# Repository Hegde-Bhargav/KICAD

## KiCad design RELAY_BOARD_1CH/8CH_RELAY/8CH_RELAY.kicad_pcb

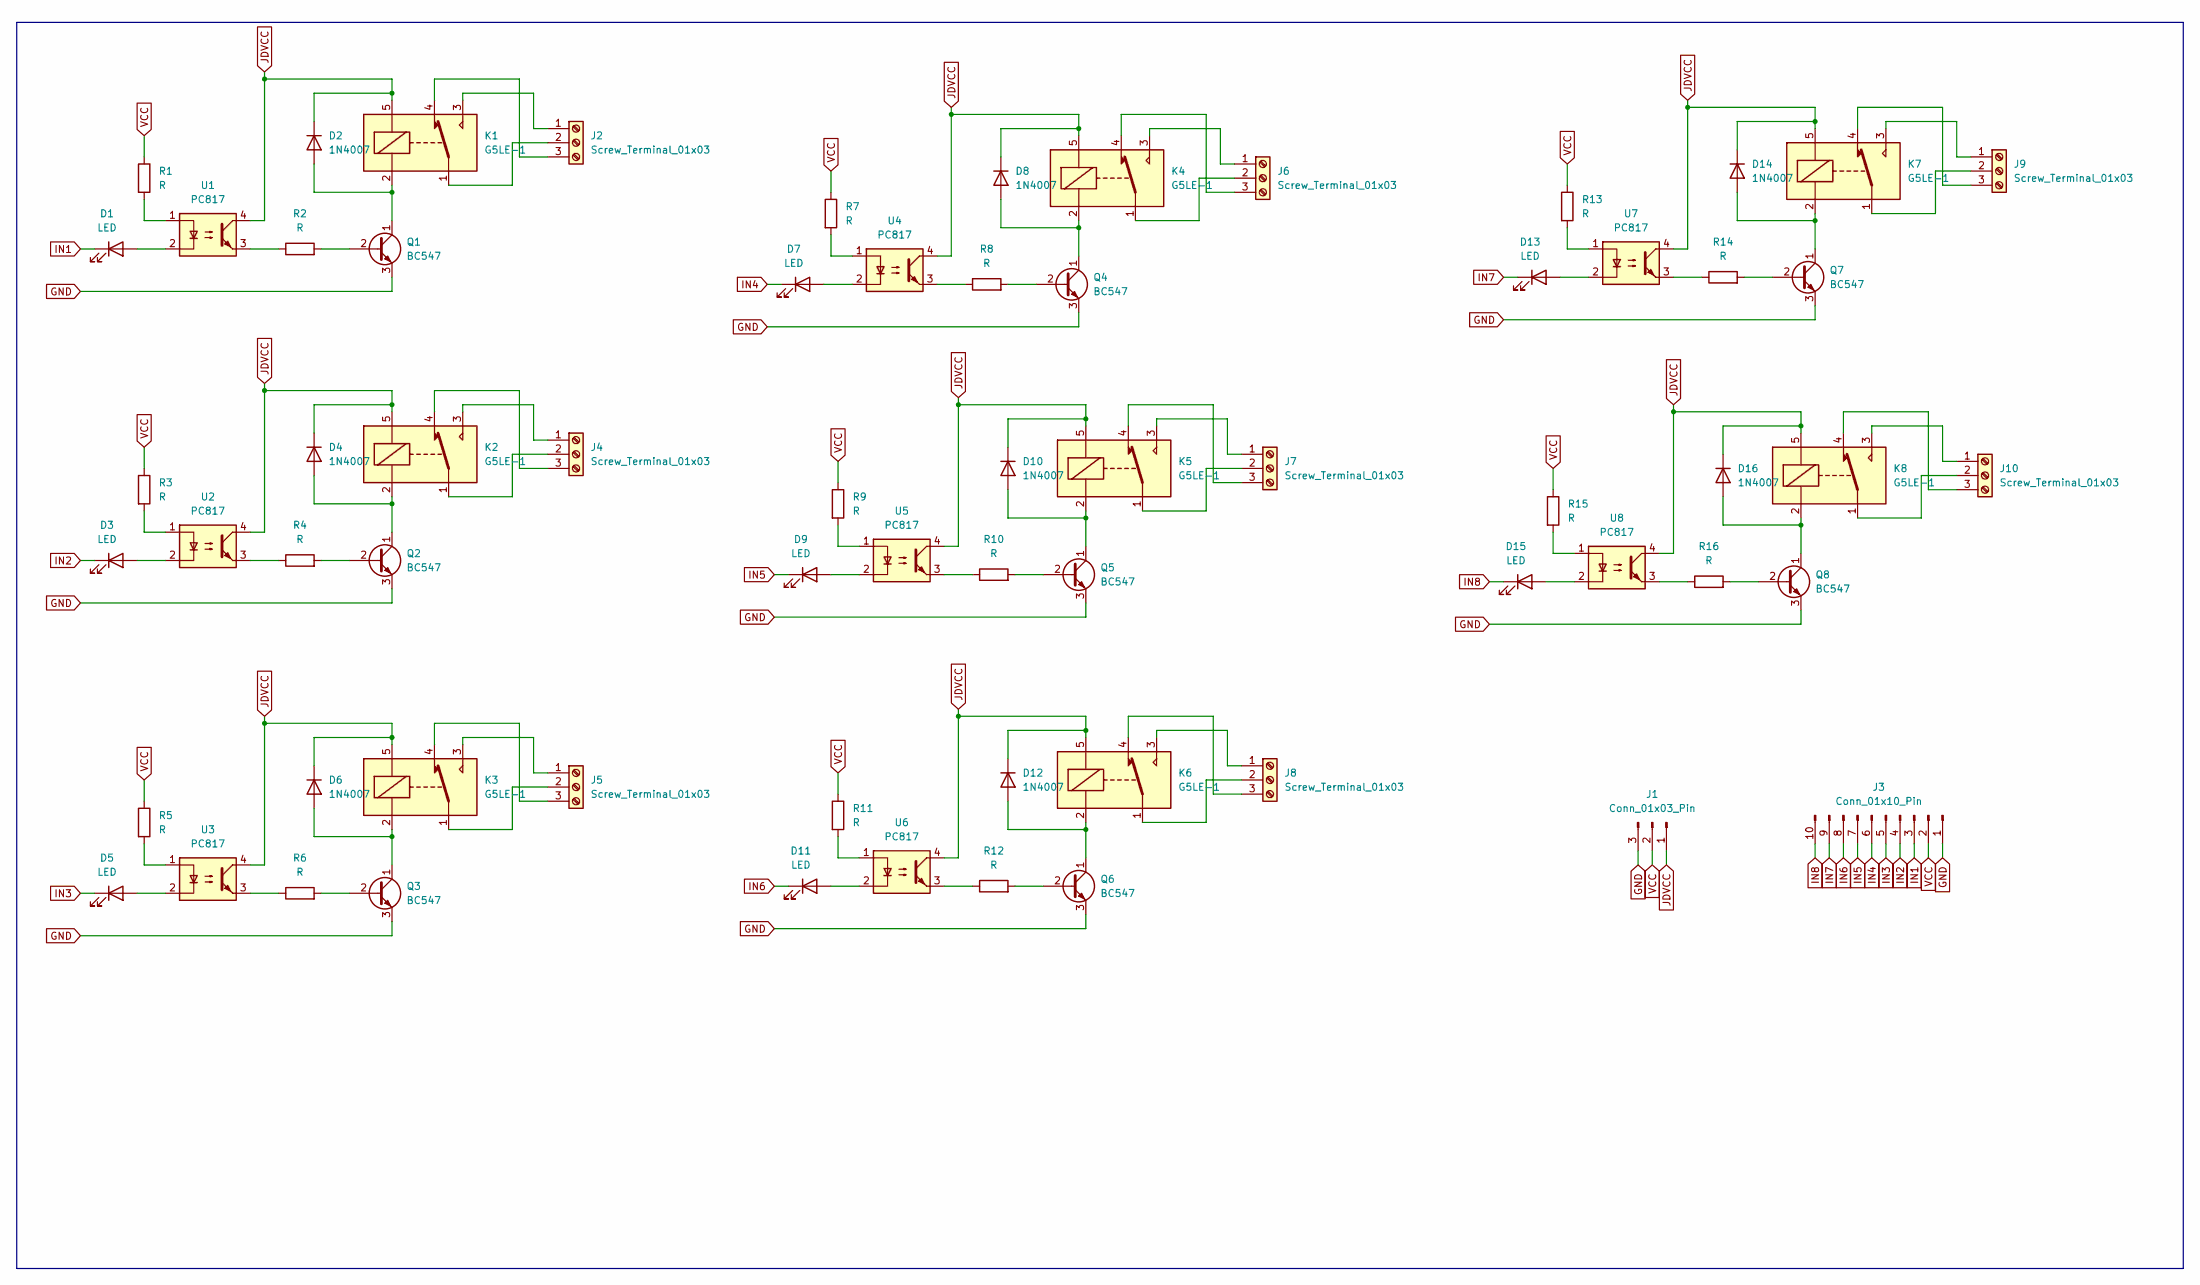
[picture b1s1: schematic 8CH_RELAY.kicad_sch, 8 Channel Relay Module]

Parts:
D1, D3, D5, D7, D9, D11, D13, D15: LED; LED_1210_3225Metric
D2, D4, D6, D8, D10, D12, D14, D16: 1N4007; D_MicroMELF
J1: Conn_01x03_Pin; PinHeader_1x03_P2.54mm_Vertical
J2, J4, J5, J6, J7, J8, J9, J10: Screw_Terminal_01x03; TerminalBlock_Phoenix_MKDS-1,5-3_1x03_P5.00mm_Horizontal
J3: Conn_01x10_Pin; PinHeader_1x10_P2.54mm_Vertical
K1, K2, K3, K4, K5, K6, K7, K8: G5LE-1; Relay_SPDT_Omron-G5LE-1
Q1, Q2, Q3, Q4, Q5, Q6, Q7, Q8: BC547; SC-59
R1, R2, R3, R4, R5, R6, R7, R8, R9, R10, R11, R12, R13, R14, R15, R16: R; R_0603_1608Metric
U1, U2, U3, U4, U5, U6, U7, U8: PC817; DIP-4_W7.62mm_SMDSocket_SmallPads

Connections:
GND: J1.3, J3.1, Q1.3 (E), Q2.3 (E), Q3.3 (E), Q4.3 (E), Q5.3 (E), Q6.3 (E), Q7.3 (E), Q8.3 (E)
IN1: D1.1 (K), J3.3
IN2: D3.1 (K), J3.4
IN3: D5.1 (K), J3.5
IN4: D7.1 (K), J3.6
IN5: D9.1 (K), J3.7
IN6: D11.1 (K), J3.8
IN7: D13.1 (K), J3.9
IN8: D15.1 (K), J3.10
JDVCC: D2.1 (K), D4.1 (K), D6.1 (K), D8.1 (K), D10.1 (K), D12.1 (K), D14.1 (K), D16.1 (K), J1.1, K1.5, K2.5, K3.5, K4.5, K5.5, K6.5, K7.5, K8.5, U1.4, U2.4, U3.4, U4.4, U5.4, U6.4, U7.4, U8.4
unnamed: D1.2 (A), U1.2
unnamed: D2.2 (A), K1.2, Q1.1 (C)
unnamed: D3.2 (A), U2.2
unnamed: D4.2 (A), K2.2, Q2.1 (C)
unnamed: D5.2 (A), U3.2
unnamed: D6.2 (A), K3.2, Q3.1 (C)
unnamed: D7.2 (A), U4.2
unnamed: D8.2 (A), K4.2, Q4.1 (C)
unnamed: D9.2 (A), U5.2
unnamed: D10.2 (A), K5.2, Q5.1 (C)
unnamed: D11.2 (A), U6.2
unnamed: D12.2 (A), K6.2, Q6.1 (C)
unnamed: D13.2 (A), U7.2
unnamed: D14.2 (A), K7.2, Q7.1 (C)
unnamed: D15.2 (A), U8.2
unnamed: D16.2 (A), K8.2, Q8.1 (C)
unnamed: J2.1, K1.3
unnamed: J2.2, K1.1
unnamed: J2.3, K1.4
unnamed: J4.1, K2.3
unnamed: J4.2, K2.1
unnamed: J4.3, K2.4
unnamed: J5.1, K3.3
unnamed: J5.2, K3.1
unnamed: J5.3, K3.4
unnamed: J6.1, K4.3
unnamed: J6.2, K4.1
unnamed: J6.3, K4.4
unnamed: J7.1, K5.3
unnamed: J7.2, K5.1
unnamed: J7.3, K5.4
unnamed: J8.1, K6.3
unnamed: J8.2, K6.1
unnamed: J8.3, K6.4
unnamed: J9.1, K7.3
unnamed: J9.2, K7.1
unnamed: J9.3, K7.4
unnamed: J10.1, K8.3
unnamed: J10.2, K8.1
unnamed: J10.3, K8.4
unnamed: Q1.2 (B), R2.2
unnamed: Q2.2 (B), R4.2
unnamed: Q3.2 (B), R6.2
unnamed: Q4.2 (B), R8.2
unnamed: Q5.2 (B), R10.2
unnamed: Q6.2 (B), R12.2
unnamed: Q7.2 (B), R14.2
unnamed: Q8.2 (B), R16.2
unnamed: R1.2, U1.1
unnamed: R2.1, U1.3
unnamed: R3.2, U2.1
unnamed: R4.1, U2.3
unnamed: R5.2, U3.1
unnamed: R6.1, U3.3
unnamed: R7.2, U4.1
unnamed: R8.1, U4.3
unnamed: R9.2, U5.1
unnamed: R10.1, U5.3
unnamed: R11.2, U6.1
unnamed: R12.1, U6.3
unnamed: R13.2, U7.1
unnamed: R14.1, U7.3
unnamed: R15.2, U8.1
unnamed: R16.1, U8.3
VCC: J1.2, J3.2, R1.1, R3.1, R5.1, R7.1, R9.1, R11.1, R13.1, R15.1

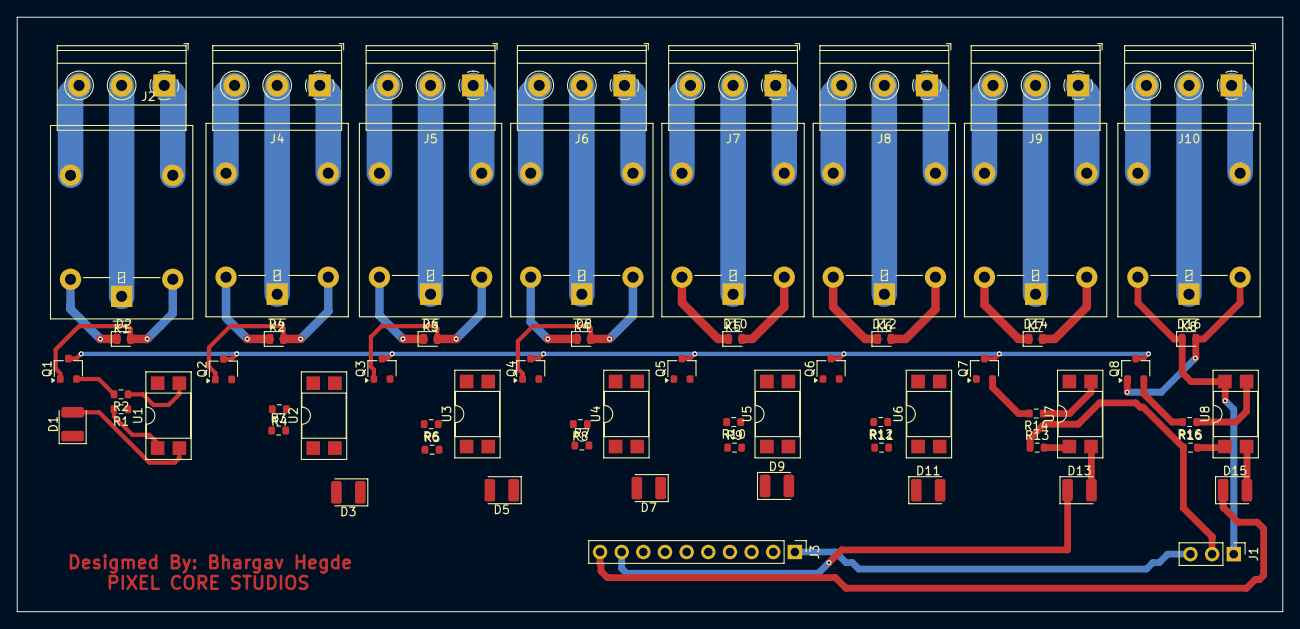
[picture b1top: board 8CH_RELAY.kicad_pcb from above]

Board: 2 copper layers, 148.5 x 69.8 mm, 66 parts (0 on the bottom side), 75 nets.

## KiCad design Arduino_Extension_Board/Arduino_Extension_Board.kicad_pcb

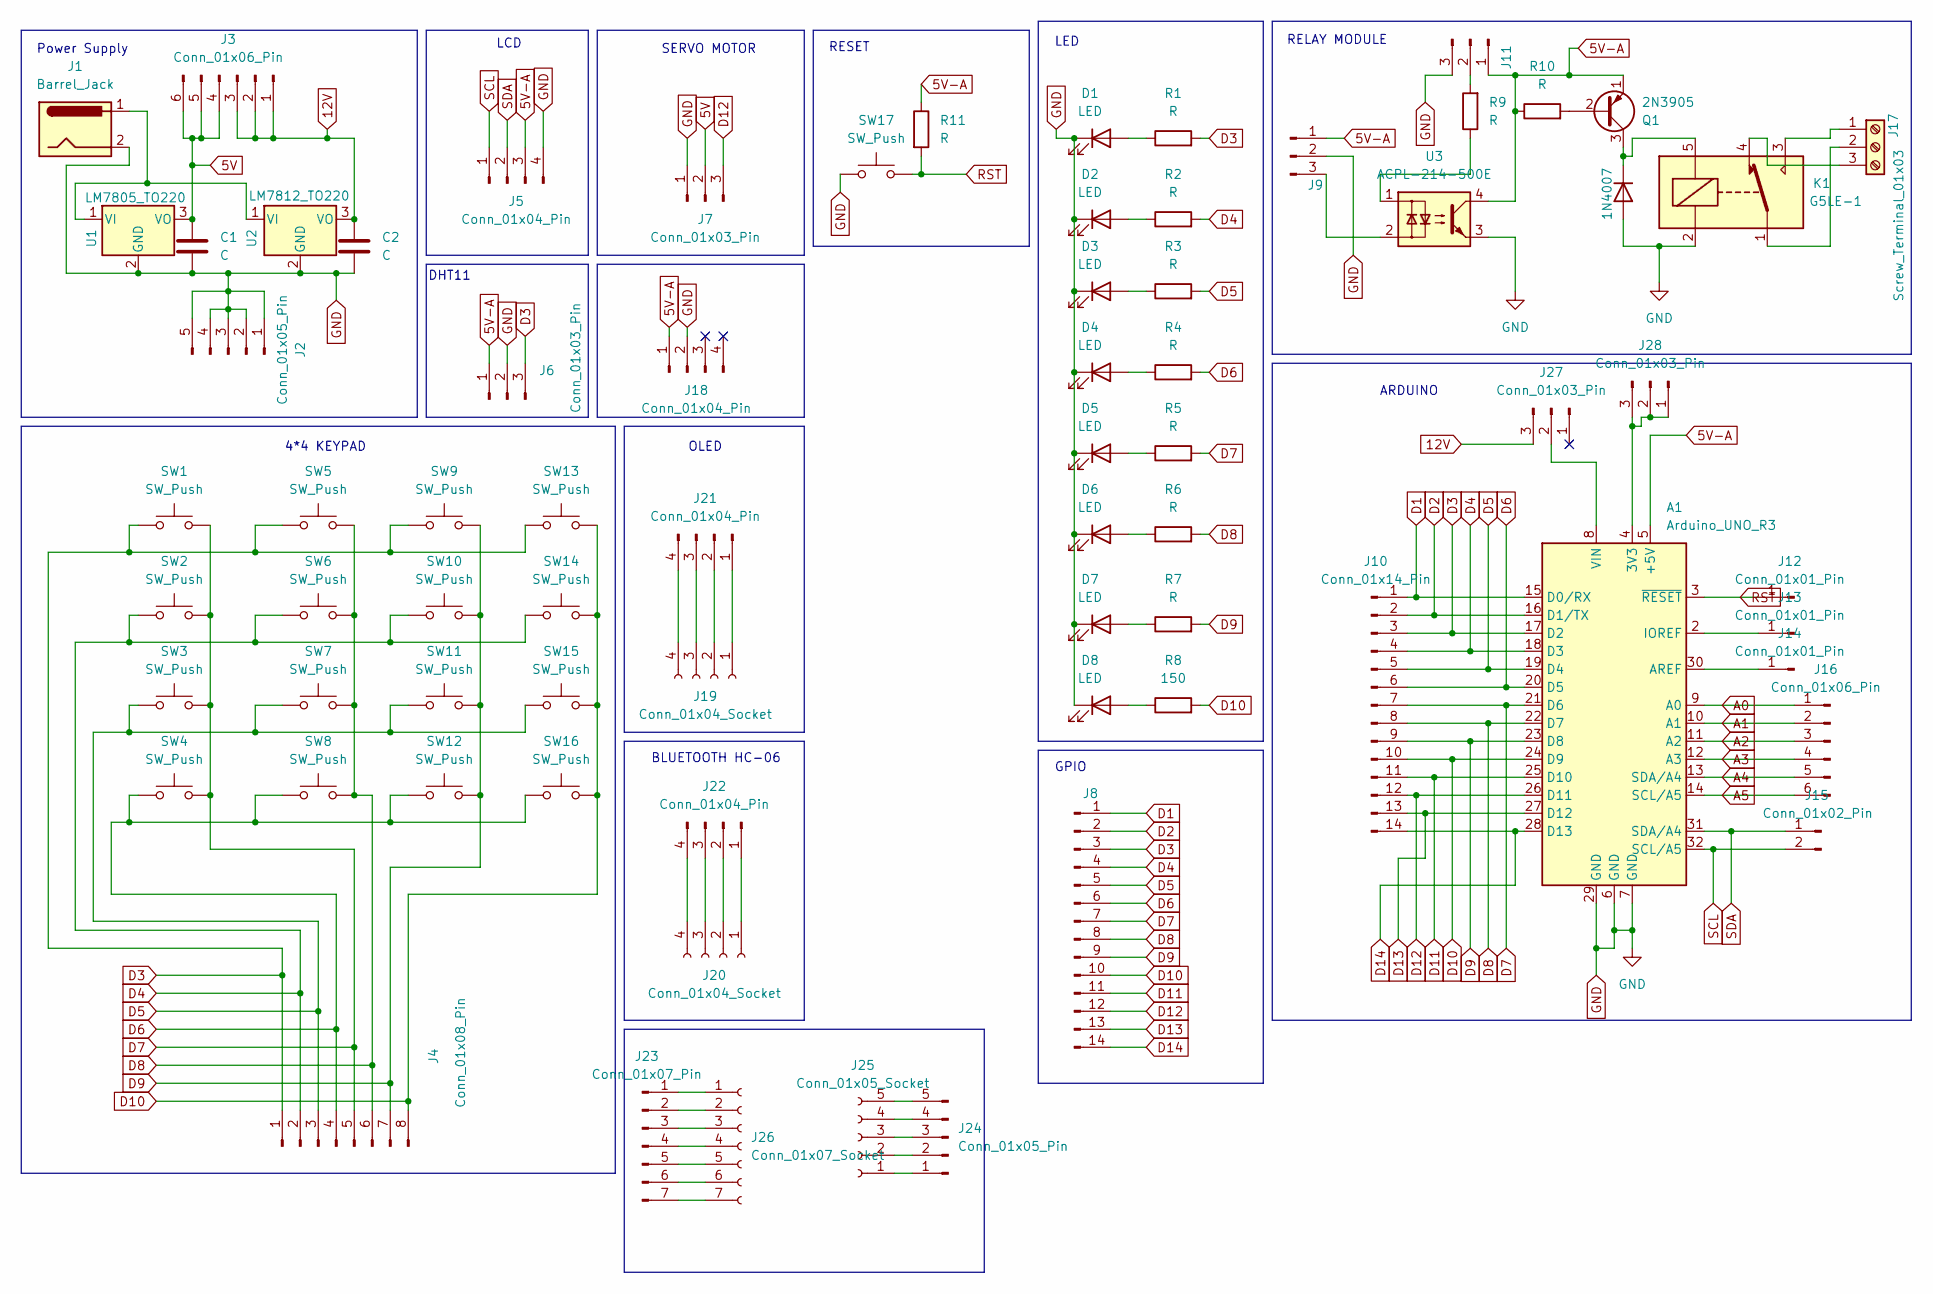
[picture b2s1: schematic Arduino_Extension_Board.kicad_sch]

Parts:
A1: Arduino_UNO_R3
C1, C2: C; C_Disc_D8.0mm_W5.0mm_P7.50mm
D1, D2, D3, D4, D5, D6, D7, D8: LED; LED_D5.0mm
D9: 1N4007; D_MiniMELF
J1: Barrel_Jack; BarrelJack_Horizontal
J2, J24: Conn_01x05_Pin; PinHeader_1x05_P2.54mm_Vertical
J3, J16: Conn_01x06_Pin; PinHeader_1x06_P2.54mm_Vertical
J4: Conn_01x08_Pin; PinHeader_1x08_P2.54mm_Vertical
J5, J18, J21, J22: Conn_01x04_Pin; PinHeader_1x04_P2.54mm_Vertical
J6: Conn_01x03_Pin; PinSocket_1x03_P2.54mm_Horizontal
J7, J11, J27, J28: Conn_01x03_Pin; PinHeader_1x03_P2.54mm_Vertical
J8, J10: Conn_01x14_Pin; PinHeader_1x14_P2.54mm_Vertical
J9: PinHeader_1x03_P2.54mm_Vertical
J12, J13, J14: Conn_01x01_Pin; PinHeader_1x01_P2.54mm_Vertical
J15: Conn_01x02_Pin; PinHeader_1x02_P2.54mm_Vertical
J17: Screw_Terminal_01x03; TerminalBlock_Phoenix_MKDS-1,5-3_1x03_P5.00mm_Horizontal
J19, J20: Conn_01x04_Socket; PinSocket_1x04_P2.54mm_Vertical
J23: Conn_01x07_Pin; PinHeader_1x07_P2.54mm_Vertical
J25: Conn_01x05_Socket; PinSocket_1x05_P2.54mm_Vertical
J26: Conn_01x07_Socket; PinSocket_1x07_P2.54mm_Vertical
K1: G5LE-1; Relay_SPDT_Omron-G5LE-1
Q1: 2N3905; SOT-223-3_TabPin2
R1, R2, R3, R4, R5, R6, R7: R; R_Axial_DIN0207_L6.3mm_D2.5mm_P10.16mm_Horizontal
R8: 150; R_Axial_DIN0207_L6.3mm_D2.5mm_P10.16mm_Horizontal
R9, R10: R; R_0603_1608Metric
R11: R; R_Axial_DIN0309_L9.0mm_D3.2mm_P15.24mm_Horizontal
SW1, SW2, SW3, SW4, SW5, SW6, SW7, SW8, SW9, SW10, SW11, SW12, SW13, SW14, SW15, SW16: SW_Push; SW_PUSH_6mm_H4.3mm
SW17: SW_Push; SW_PUSH_6mm
U1: LM7805_TO220; TO-220-3_Vertical
U2: LM7812_TO220; TO-220-3_Vertical
U3: ACPL-214-500E; SOP-4_4.4x2.6mm_P1.27mm

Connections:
5V: C1.1, J3.4, J3.5, J3.6, J7.2, U1.3 (VO)
5V-A: A1.5 (+5V), J5.3, J6.1, J9.1, J11.1, J18.1, Q1.1 (E), R10.1, R11.1, U3.4
12V: C2.1, J3.1, J3.2, J3.3, J27.3, U2.3 (VO)
A0: A1.9 (A0), J16.1
A1: A1.10 (A1), J16.2
A2: A1.11 (A2), J16.3
A3: A1.12 (A3), J16.4
A4: A1.13 (SDA/A4), J16.5
A5: A1.14 (SCL/A5), J16.6
D1: A1.15 (D0/RX), J8.1, J10.1
D2: A1.16 (D1/TX), J8.2, J10.2
D3: A1.17 (D2), J4.1, J6.3, J8.3, J10.3, R1.2, SW1.1, SW5.1, SW9.1, SW13.1
D4: A1.18 (D3), J4.2, J8.4, J10.4, R2.2, SW2.1, SW6.1, SW10.1, SW14.1
D5: A1.19 (D4), J4.3, J8.5, J10.5, R3.2, SW3.1, SW7.1, SW11.1, SW15.1
D6: A1.20 (D5), J4.4, J8.6, J10.6, R4.2, SW4.1, SW8.1, SW12.1, SW16.1
D7: A1.21 (D6), J4.5, J8.7, J10.7, R5.2, SW1.2, SW2.2, SW3.2, SW4.2
D8: A1.22 (D7), J4.6, J8.8, J10.8, R6.2, SW5.2, SW6.2, SW7.2, SW8.2
D9: A1.23 (D8), J4.7, J8.9, J10.9, R7.2, SW9.2, SW10.2, SW11.2, SW12.2
D10: A1.24 (D9), J4.8, J8.10, J10.10, R8.2, SW13.2, SW14.2, SW15.2, SW16.2
D11: A1.25 (D10), J8.11, J10.11
D12: A1.26 (D11), J7.3, J8.12, J10.12
D13: A1.27 (D12), J8.13, J10.13
D14: A1.28 (D13), J8.14, J10.14
GND: A1.6 (GND), A1.7 (GND), A1.29 (GND), C1.2, C2.2, D1.1 (K), D2.1 (K), D3.1 (K), D4.1 (K), D5.1 (K), D6.1 (K), D7.1 (K), D8.1 (K), D9.2 (A), J1.2, J2.1, J2.2, J2.3, J2.4, J2.5, J5.4, J6.2, J7.1, J9.2, J11.3, J18.2, K1.2, SW17.1, U1.2 (GND), U2.2 (GND), U3.3
unnamed: A1.4 (3V3), J28.1, J28.2, J28.3
unnamed: A1.30 (AREF), J14.1
unnamed: A1.2 (IOREF), J13.1
unnamed: A1.8 (VIN), J27.2
unnamed: D1.2 (A), R1.1
unnamed: D2.2 (A), R2.1
unnamed: D3.2 (A), R3.1
unnamed: D4.2 (A), R4.1
unnamed: D5.2 (A), R5.1
unnamed: D6.2 (A), R6.1
unnamed: D7.2 (A), R7.1
unnamed: D8.2 (A), R8.1
unnamed: D9.1 (K), K1.5, Q1.3 (C)
unnamed: J9.3, U3.2
unnamed: J11.2, R9.2
unnamed: J17.1, K1.3
unnamed: J17.2, K1.1
unnamed: J17.3, K1.4
unnamed: J19.1, J21.1
unnamed: J19.2, J21.2
unnamed: J19.3, J21.3
unnamed: J19.4, J21.4
unnamed: J20.1, J22.1
unnamed: J20.2, J22.2
unnamed: J20.3, J22.3
unnamed: J20.4, J22.4
unnamed: J23.1, J26.1
unnamed: J23.2, J26.2
unnamed: J23.3, J26.3
unnamed: J23.4, J26.4
unnamed: J23.5, J26.5
unnamed: J23.6, J26.6
unnamed: J23.7, J26.7
unnamed: J24.1, J25.1
unnamed: J24.2, J25.2
unnamed: J24.3, J25.3
unnamed: J24.4, J25.4
unnamed: J24.5, J25.5
unnamed: Q1.2 (B), R10.2
unnamed: R9.1, U3.1
unnamed: J1.1, U1.1 (VI), U2.1 (VI)
RST: A1.3 (~RESET), J12.1, R11.2, SW17.2
SCL: A1.32 (SCL/A5), J5.1, J15.2
SDA: A1.31 (SDA/A4), J5.2, J15.1

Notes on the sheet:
RESET
LCD
BLUETOOTH HC-06
ARDUINO
GPIO
4*4 KEYPAD
OLED
LED
RELAY MODULE
Power Supply
DHT11
SERVO MOTOR

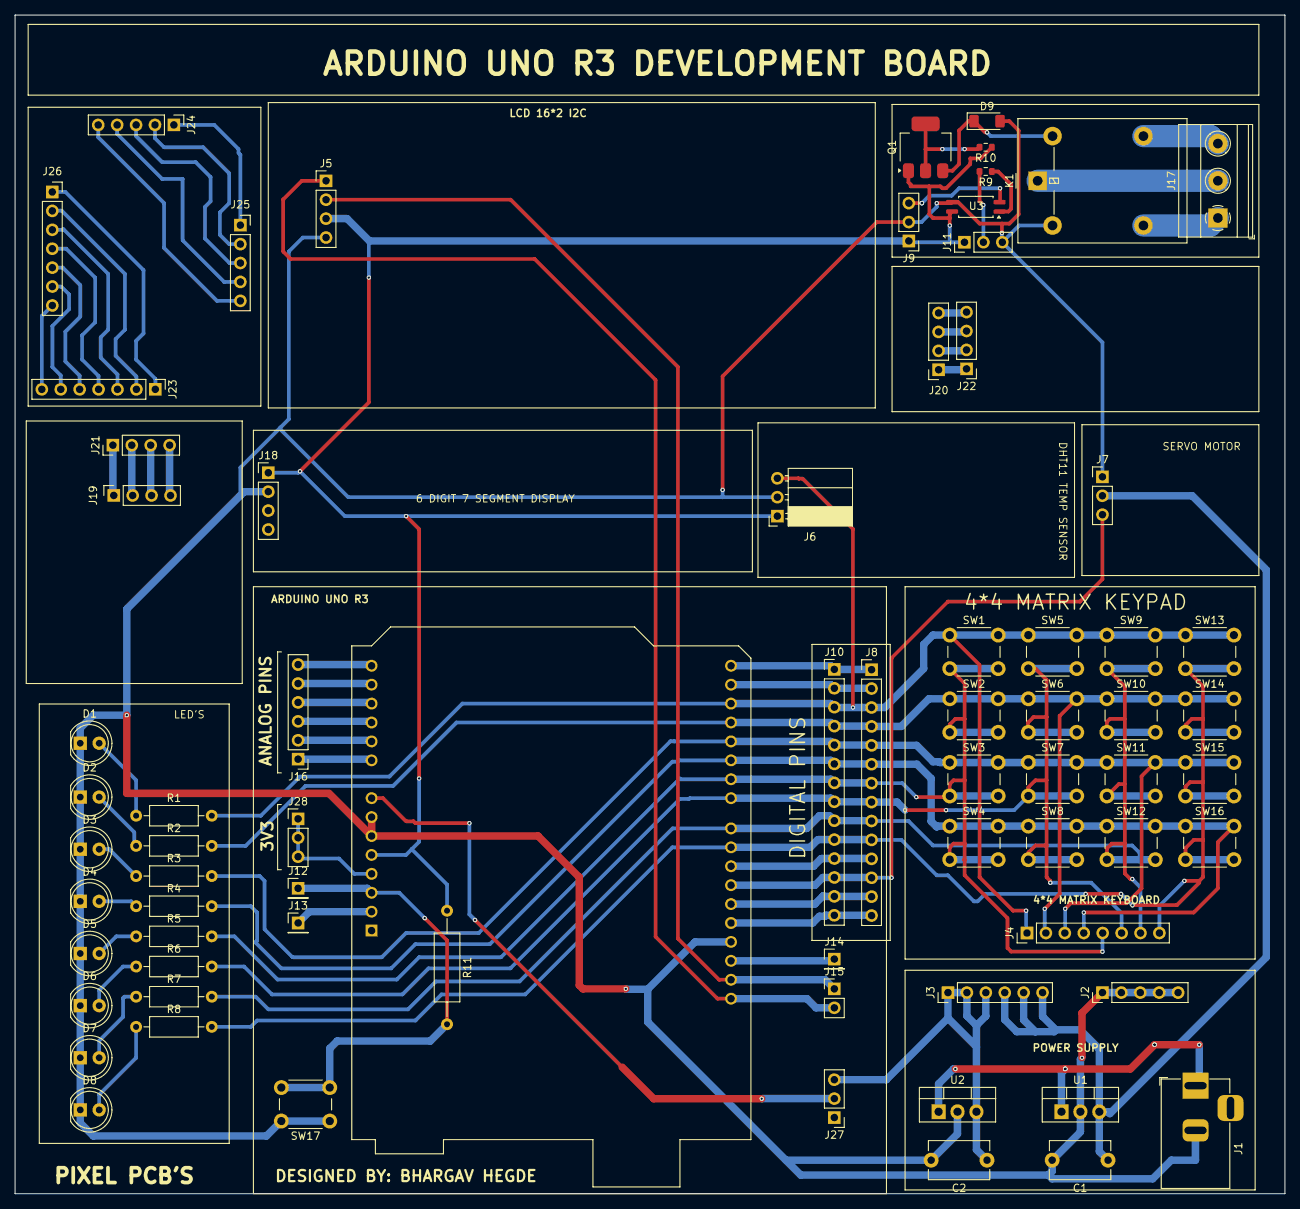
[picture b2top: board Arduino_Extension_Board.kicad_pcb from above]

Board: 2 copper layers, 170.5 x 158.2 mm, 73 parts (0 on the bottom side), 68 nets.

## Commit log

2026-03-31 first upload
2026-03-31 3d images
